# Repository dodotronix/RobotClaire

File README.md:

# ROBOT CLAIRE
This project is the result of three years of development from my high school
years. The main goal was to build my own robot from scratch, without using
common construction parts that are readily available in many hobbyist shops
today.

At the time when I was creating my robot, open-source CAD programs weren’t at a
sufficient level to design something that could be sent to a factory for
fabrication. For this reason, the mechanical design was created using Inventor
2013, while the electronic design was done using KiCad. The project has already
gone through three upgrades, but the first one wasn’t documented. However, I
did take some photos to capture the atmosphere of the very first steps in
development ([claire-rev0](https://drive.google.com/open?id=1PmOoYiifd_Xv0sS2DL9yxbEeKM7cLnv_)).

## NAVIGATION IN PROJECT
In the following folders, you will find README.md files with more detailed
descriptions of the content. Some folders also include additional information,
such as installation and execution instructions, particularly in directories
containing software. Please note that this repository is still under
development, and not all folders have been fully uploaded yet.

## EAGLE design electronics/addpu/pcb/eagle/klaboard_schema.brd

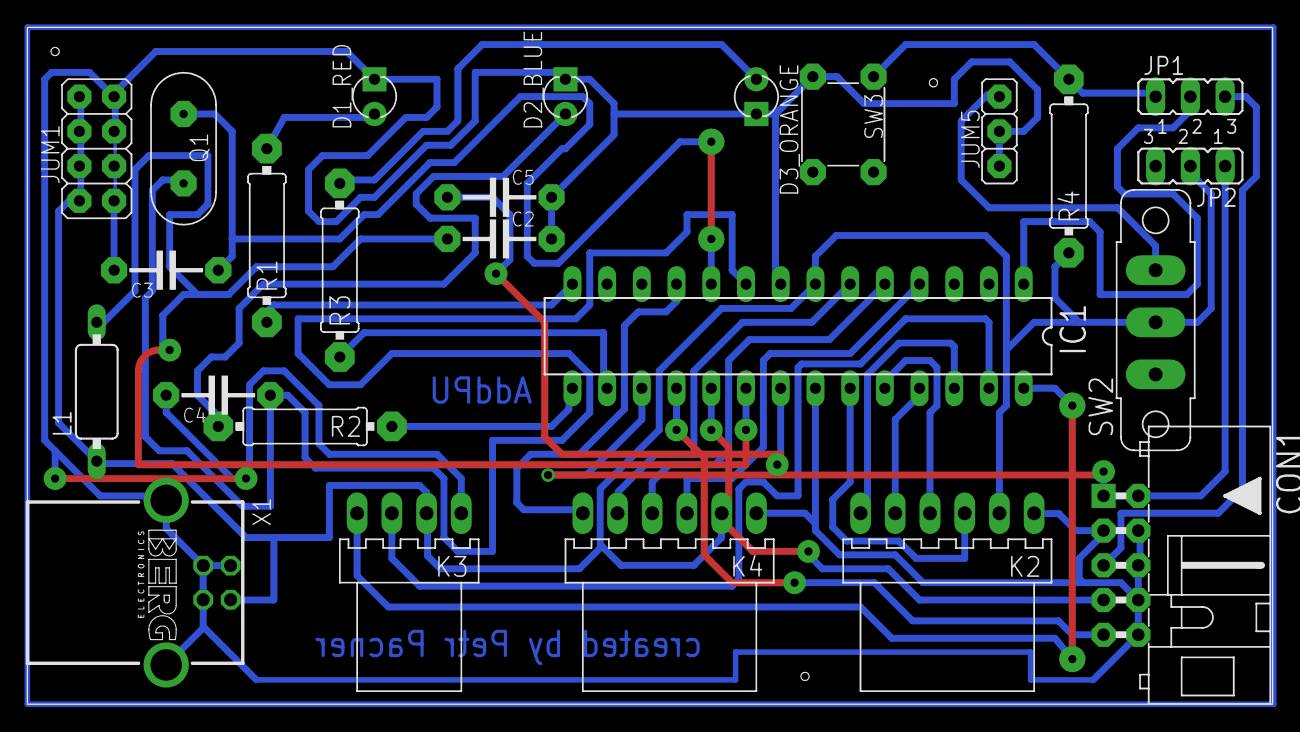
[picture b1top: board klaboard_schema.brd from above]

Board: 2 copper layers, 91.1 x 49.5 mm, 25 parts (0 on the bottom side), 30 nets.

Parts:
C2, C5: 100nF; C-7,5
C3, C4: 22picoF; C-7,5
CON1: MLW10_90; MLW10A
D1_RED: ERROR; LED_3
D2_BLUE: TWI-in_progress; LED_3
D3_ORANGE: Program_ready; LED_3
IC1: MEGA8-P; DIL28-3
JP1, JP2: JP2
JUM1: S2G4_JUMP; S2G4_JUM
JUM5: S1G3_JUMP; S1G3_JUM
K2: Sensor_signal; PSH02-06W
K3: I2C; PSH02-04W
K4: Enkodery; PSH02-06W
L1: 10microH; SBC10
Q1: 16MHz; HC-49U
R1: 200; R-12,7
R2: 100; R-12,7
R3: 180; R-12,7
R4: 10k; R-12,7
SW2: P-B144
SW3: P-B1720
X1: RPi; PN61729-S

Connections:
+5V: IC1.7, JP2.2, JUM1.2_1, JUM1.2_2, JUM1.2_3, JUM1.2_4, K2.2, K3.2, K4.2, L1.1, R4.1, SW2.2, X1.1
GND: C2.2, C3.2, C4.2, C5.2, CON1.3, CON1.4, CON1.6, CON1.8, CON1.10, D1_RED.K, D2_BLUE.K, D3_ORANGE.K, IC1.8, IC1.22, JUM1.1_1, JUM1.1_2, JUM1.1_3, JUM1.1_4, JUM5.1, JUM5.2, K2.1, K3.1, K4.1, SW3.1, X1.2, X1.3, X1.4, X1.S1, X1.S2
unnamed: IC1.28, K3.4
unnamed: C2.1, IC1.20, L1.2
unnamed: IC1.4, K4.3
unnamed: IC1.5, K4.4
unnamed: IC1.6, K4.5
unnamed: IC1.11, K4.6
unnamed: C3.1, IC1.10, Q1.1
unnamed: C4.1, IC1.9, Q1.2
unnamed: C5.1, IC1.21
unnamed: IC1.14, R1.1
unnamed: IC1.27, K3.3
unnamed: CON1.1, IC1.17
unnamed: CON1.2, JP2.1
unnamed: IC1.1, JP1.2
unnamed: JUM5.3, SW2.3
unnamed: CON1.7, IC1.19
unnamed: CON1.9, IC1.18
unnamed: IC1.15, R2.1
unnamed: IC1.16, R3.1
unnamed: D3_ORANGE.A, R3.2
unnamed: D2_BLUE.A, R2.2
unnamed: D1_RED.A, R1.2
unnamed: IC1.26, K2.6
unnamed: IC1.25, K2.5
unnamed: IC1.24, K2.4
unnamed: IC1.23, K2.3
unnamed: JP1.1, R4.2, SW3.2
unnamed: CON1.5, JP1.3

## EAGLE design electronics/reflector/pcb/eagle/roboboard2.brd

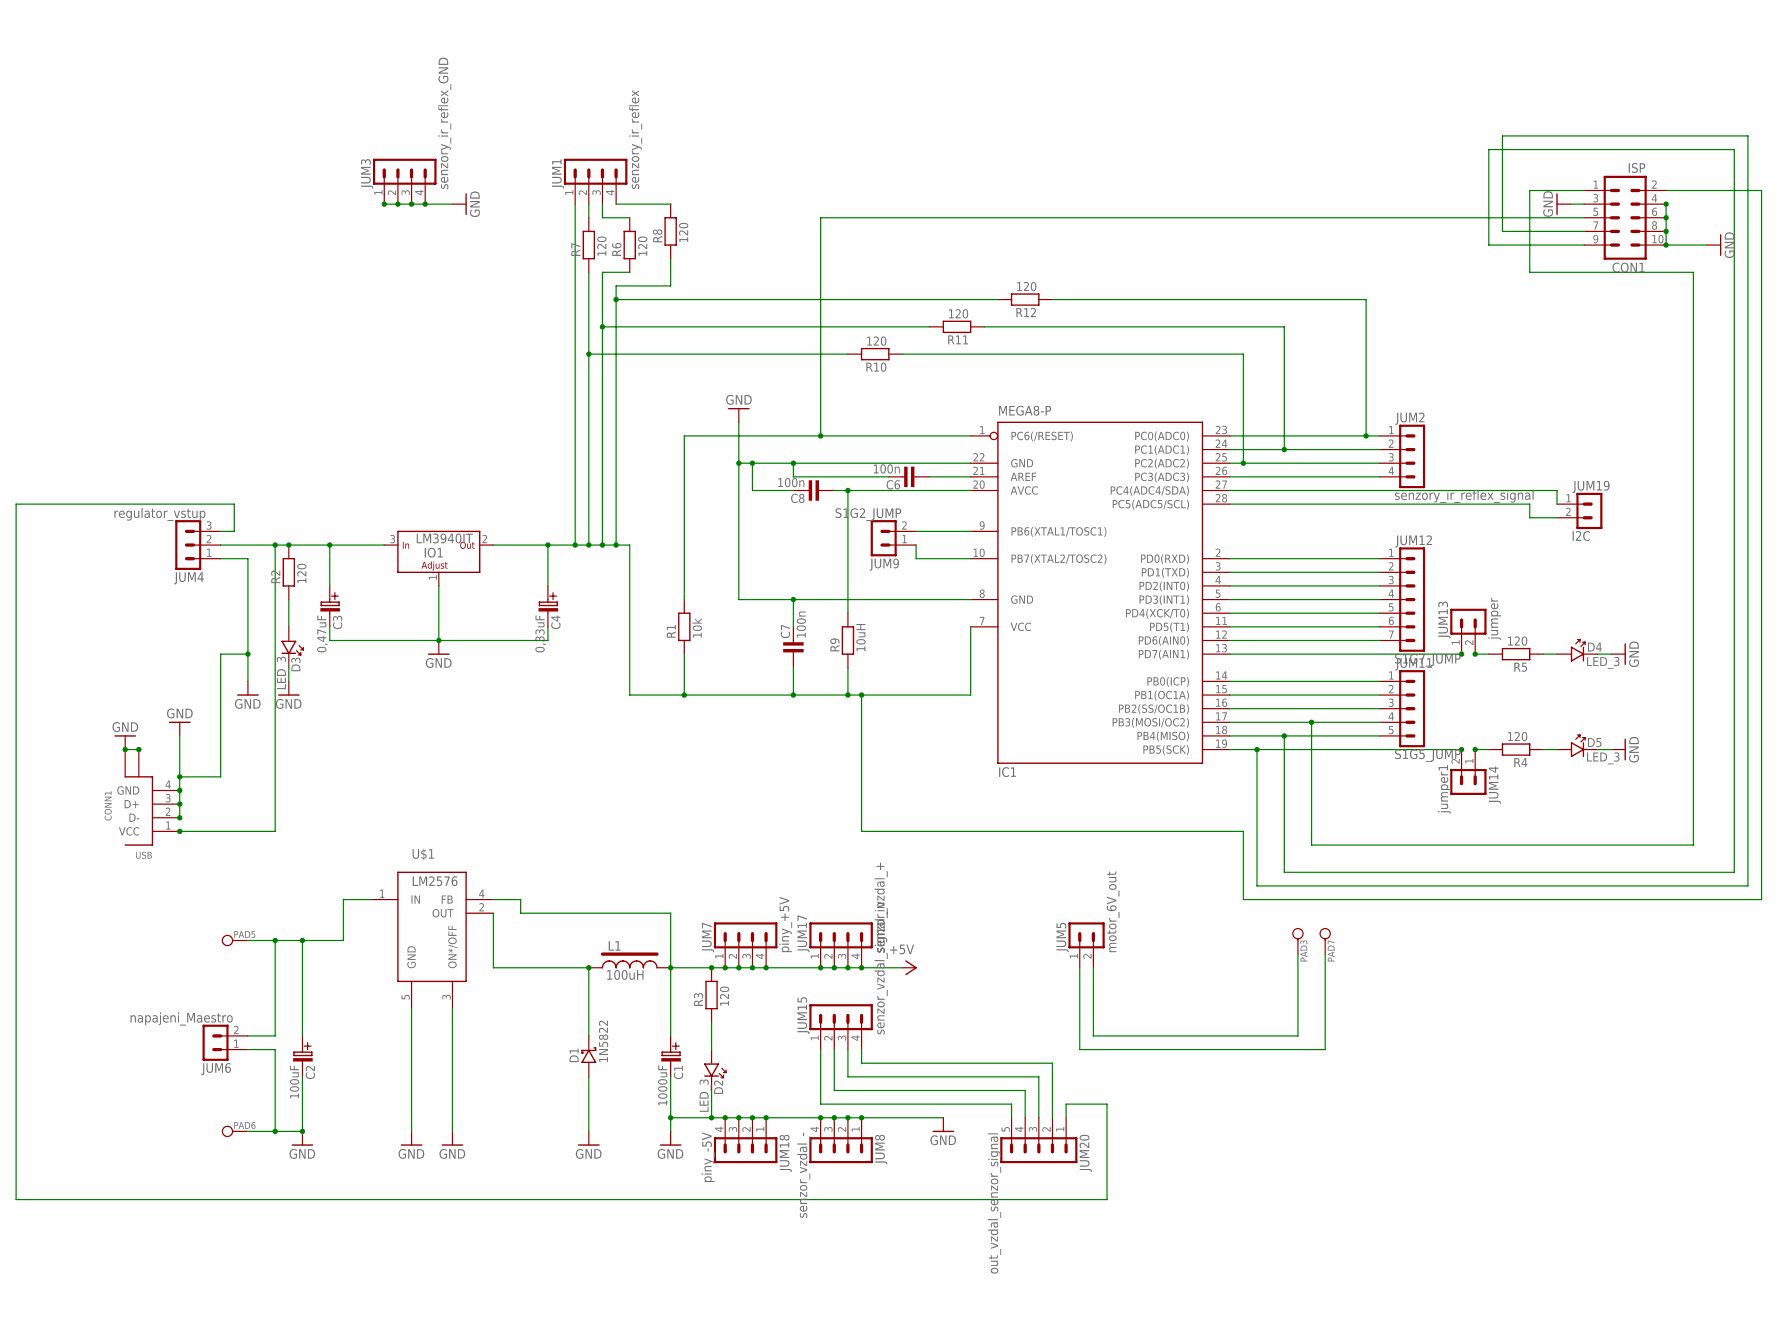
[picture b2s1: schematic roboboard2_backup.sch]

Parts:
C1: 1000uF; C-EL_5
C2: 100uF; C-EL_5
C3: 0,47uF; C-EL_5
C4: 0,33uF; C-EL_3,5
C6, C7, C8: 100n; C-2,5
CON1: ISP; MLW10A
CONN1: USB; PN61729
D1: 1N5822; TO-220AC
D2, D3, D4, D5: LED_3
IC1: MEGA8-P; DIL28-3
IO1: LM3940IT; TO-220
JUM1: senzory_ir_reflex; S1G4_JUM
JUM2: senzory_ir_reflex_signal; S1G4_JUM
JUM3: senzory_ir_reflex_GND; S1G4_JUM
JUM4: regulator_vstup; S1G3_JUM
JUM5: motor_6V_out; S1G2_JUM
JUM6: napajeni_Maestro; S1G2_JUM
JUM7: piny_+5V; S1G4_JUM
JUM8: senzor_vzdal_-; S1G4_JUM
JUM9: S1G2_JUMP; S1G2_JUM
JUM11: S1G5_JUMP; S1G5_JUM
JUM12: S1G7_JUMP; S1G7_JUM
JUM13: jumper; S1G2_JUM
JUM14: jumper1; S1G2_JUM
JUM15: senzor_vzdal_signal_in; S1G4_JUM
JUM17: senzor_vzdal_+; S1G4_JUM
JUM18: piny_-5V; S1G4_JUM
JUM19: I2C; S1G2_JUM
JUM20: out_vzdal_senzor_signal; S1G5_JUM
L1: 100uH; FED_2200
PAD3: motor_6V_in; PAD_1
PAD5: 11,1V; PAD_1
PAD6: PAD_1-; PAD_1
PAD7: 6V_motor; PAD_1
R1: 10k; R-10
R2, R3, R4, R5, R6, R7, R8, R10, R11, R12: 120; R-10
R9: 10uH; R-10
U$1: LM2576

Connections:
+5V: C1.C+ (C_EL+), JUM7.1, JUM7.2, JUM7.3, JUM7.4, JUM17.1, JUM17.2, JUM17.3, JUM17.4, L1.2, R3.2, U$1.4 (FB)
GND: C1.C- (C_EL-), C2.C- (C_EL-), C3.C- (C_EL-), C4.C- (C_EL-), C6.2, C7.2, C8.2, CON1.3, CON1.4, CON1.6, CON1.8, CON1.10, CONN1.2 (D-), CONN1.3 (D+), CONN1.4 (GND), CONN1.P$1, CONN1.P$2, D1.A, D2.K, D3.K, D4.K, D5.K, IC1.8 (GND), IC1.22 (GND), IO1.1 (ADJ), JUM3.1, JUM3.2, JUM3.3, JUM3.4, JUM4.1, JUM6.1, JUM8.1, JUM8.2, JUM8.3, JUM8.4, JUM18.1, JUM18.2, JUM18.3, JUM18.4, PAD6.1, U$1.3 (ON*/OFF), U$1.5 (GND)
unnamed: D1.K, L1.1, U$1.2 (OUT)
unnamed: C6.1, IC1.21 (AREF)
unnamed: C8.1, IC1.20 (AVCC), R9.2
unnamed: CON1.5, IC1.1 (PC6(/RESET)), R1.2
unnamed: IC1.24 (PC1(ADC1)), JUM2.2, R11.1
unnamed: IC1.25 (PC2(ADC2)), JUM2.3, R10.1
unnamed: IC1.23 (PC0(ADC0)), JUM2.1, R12.1
unnamed: IC1.26 (PC3(ADC3)), JUM2.4
unnamed: IC1.27 (PC4(ADC4/SDA)), JUM19.1
unnamed: IC1.28 (PC5(ADC5/SCL)), JUM19.2
unnamed: IC1.2 (PD0(RXD)), JUM12.1
unnamed: IC1.3 (PD1(TXD)), JUM12.2
unnamed: IC1.4 (PD2(INT0)), JUM12.3
unnamed: IC1.5 (PD3(INT1)), JUM12.4
unnamed: IC1.6 (PD4(XCK/T0)), JUM12.5
unnamed: IC1.11 (PD5(T1)), JUM12.6
unnamed: IC1.12 (PD6(AIN0)), JUM12.7
unnamed: IC1.13 (PD7(AIN1)), JUM13.1
unnamed: IC1.14 (PB0(ICP)), JUM11.1
unnamed: IC1.15 (PB1(OC1A)), JUM11.2
unnamed: CON1.1, IC1.17 (PB3(MOSI/OC2)), JUM11.4
unnamed: IC1.16 (PB2(SS/OC1B)), JUM11.3
unnamed: CON1.9, IC1.18 (PB4(MISO)), JUM11.5
unnamed: CON1.7, IC1.19 (PB5(SCK)), JUM14.2
unnamed: JUM5.1, PAD7.1
unnamed: IC1.9 (PB6(XTAL1/TOSC1)), JUM9.2
unnamed: D4.A, R5.1
unnamed: JUM4.3, JUM20.1
unnamed: D3.A, R2.1
unnamed: D2.A, R3.1
unnamed: C2.C+ (C_EL+), JUM6.2, PAD5.1, U$1.1 (IN)
unnamed: JUM5.2, PAD3.1
unnamed: IC1.10 (PB7(XTAL2/TOSC2)), JUM9.1
unnamed: D5.A, R4.1
unnamed: JUM13.2, R5.2
unnamed: JUM1.2, R7.2
unnamed: JUM1.3, R6.2
unnamed: JUM1.4, R8.2
unnamed: JUM14.1, R4.2
unnamed: JUM15.1, JUM20.5
unnamed: JUM15.2, JUM20.4
unnamed: JUM15.3, JUM20.3
unnamed: JUM15.4, JUM20.2
unnamed: C4.C+ (C_EL+), C7.1, CON1.2, IC1.7 (VCC), IO1.2 (OUT), JUM1.1, R1.1, R6.1, R7.1, R8.1, R9.1, R10.2, R11.2, R12.2
VCC: C3.C+ (C_EL+), CONN1.1 (VCC), IO1.3 (IN), JUM4.2, R2.2

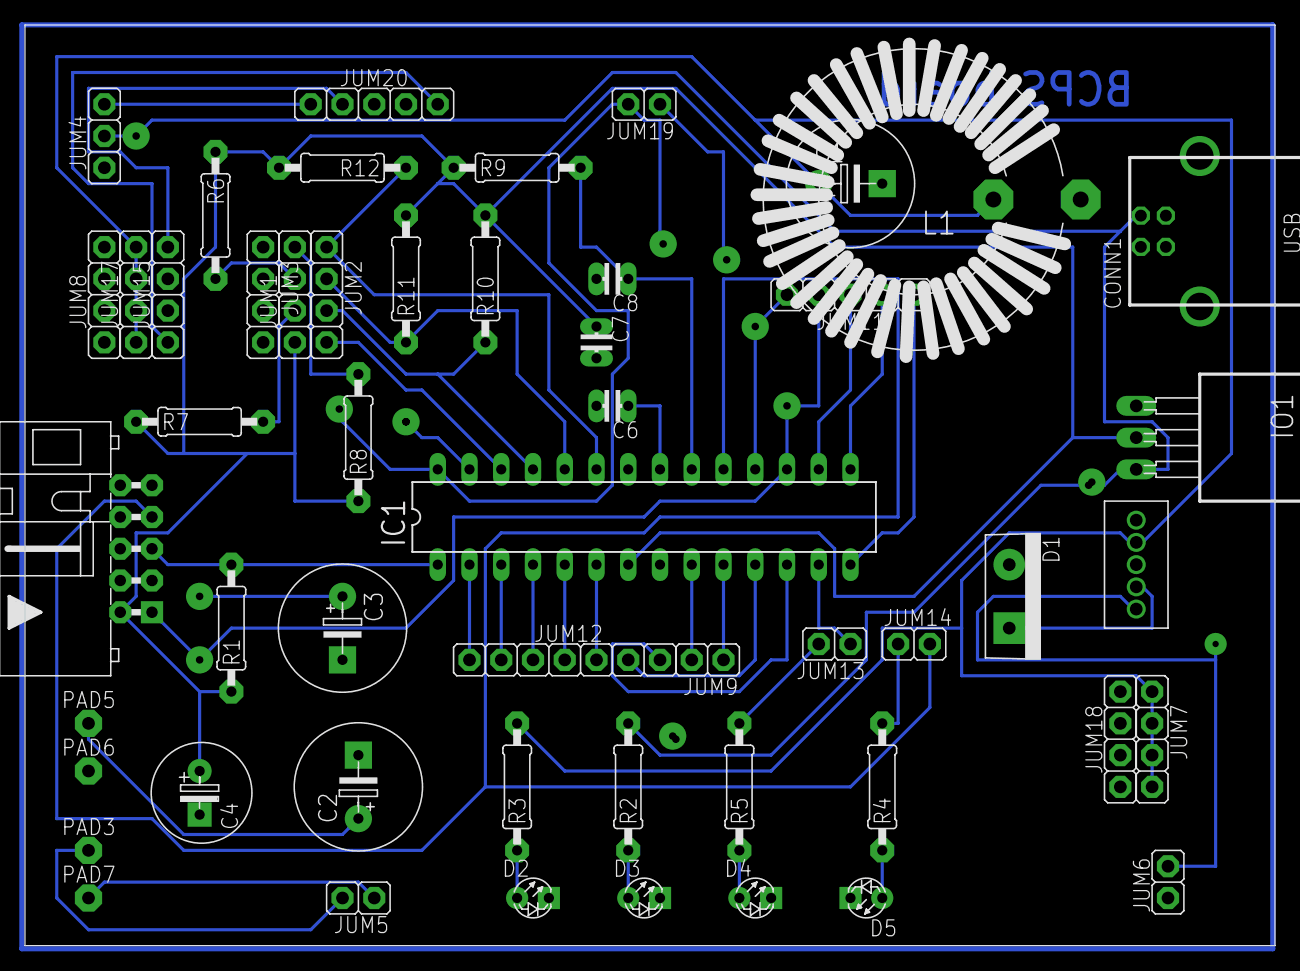
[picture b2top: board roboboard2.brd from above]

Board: 2 copper layers, 100.0 x 73.6 mm, 52 parts (0 on the bottom side), 47 nets.

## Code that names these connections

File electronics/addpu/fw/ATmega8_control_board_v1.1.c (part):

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
/* POPIS FCE PROGRAME PRO CTENI ENKODERU
 * enkodery jsou sledovany jen kdyz je na vstupnich pinech log1 -> je tedy nutne pouzit AVR fci interrupt (preruseni)
 * PD2 = INT0 a PD3 = INT1 interupt piny
 * Enkoder_Motor0 - A == Pin PD2; B == Pin PD4
 * Enkoder_Motor1 - A == Pin PD3; B == Pin PD5
 * na pinech PD2 a PD3 je zapnut interrupt -> jakmile se zmeni hodnota pinu PD2 nebo PD3 na log1  program zacne piny sledovat
 * -> pricte nebo odecte jednotku k promenne EnkValue0 nebo 1  podle toho, jestli se robot pohybuje dopredu nebo dozadu
 
*  tzn. kdyz ma senzor A log1 a B ma log0 odecte se jednicka v pripade log1 se jednicka pricte
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  // MCUCR - registr ktery nastavuje, na co bude externi interrupt reagovat viz. dokumentace atmega8
  // ISC0 == INT0
  // ISC1 == INT1
  GICR |= (1<<INT1) | (1<<INT0); // povoli externi interrupt piny INT0(PD2) a INT1(PD3)
  sei (); // zapne fci interrupt
}

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
// makro ISR()  funguje jako ovladac interuptu s vektorem, ktery je v zavorce jako parametr fce
// fce pro sledovani enkoderu 0
ISR (INT0_vect) // vector INT0 (PD2)
{
      if ((PIND &= 0x10) == 0) // vymaskuje pin 4 (vodic B [bily]); je na vstupu log0?
      {
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

// fce pro sledovani  enkoderu 1
ISR (INT1_vect) //vektor INT1 (PD3)
{
      if ((PIND &= 0x20) == 0) // vymaskuje pin 5 (vodic B [bily]); je na vstupu log0?
      {
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
int main ()
{
     DDRB = 0x07; // inicializace vystupniho pinu PB5
     PORTB |= 0x01; // rozsvit vsechny LED (poradi: zluta, modra, cervena)

    ADinitialize ();
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
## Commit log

2020-01-30 new README.md
2020-01-30 created introduction - readme
2020-01-30 text correction - share link
2020-01-30 text correction - readme
2020-01-30 added video link - readme
2020-02-05 added CAD model from inventor 2013
2020-02-05 added reflector pcb design
2020-02-19 markdown syntax test - introduction photo
2020-02-19 shared picture fixed markdown syntax
2020-02-19 shared picture from google disk - fetching test
2020-03-22 Robot_system.drawio
2020-03-22 Robot_system.svg
2020-03-22 drawings moved to doc folder
2020-03-22 new submodules sensors
2020-03-29 changed size of themain picture
2020-03-29 bigger size of main picture
2020-03-29 main picture change of size
2020-09-30 Raw files from original project Robot Claire
2020-09-30 updated module sensors
2025-04-02 updated readme picture
2025-04-02 fixed readme
2025-04-02 Readme update

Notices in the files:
parts and their libraries:
Copyright (C) PaJa 2001-2014
Copyright (C) PaJa 2011-2014
Copyright (C) PaJa 2001-2010
